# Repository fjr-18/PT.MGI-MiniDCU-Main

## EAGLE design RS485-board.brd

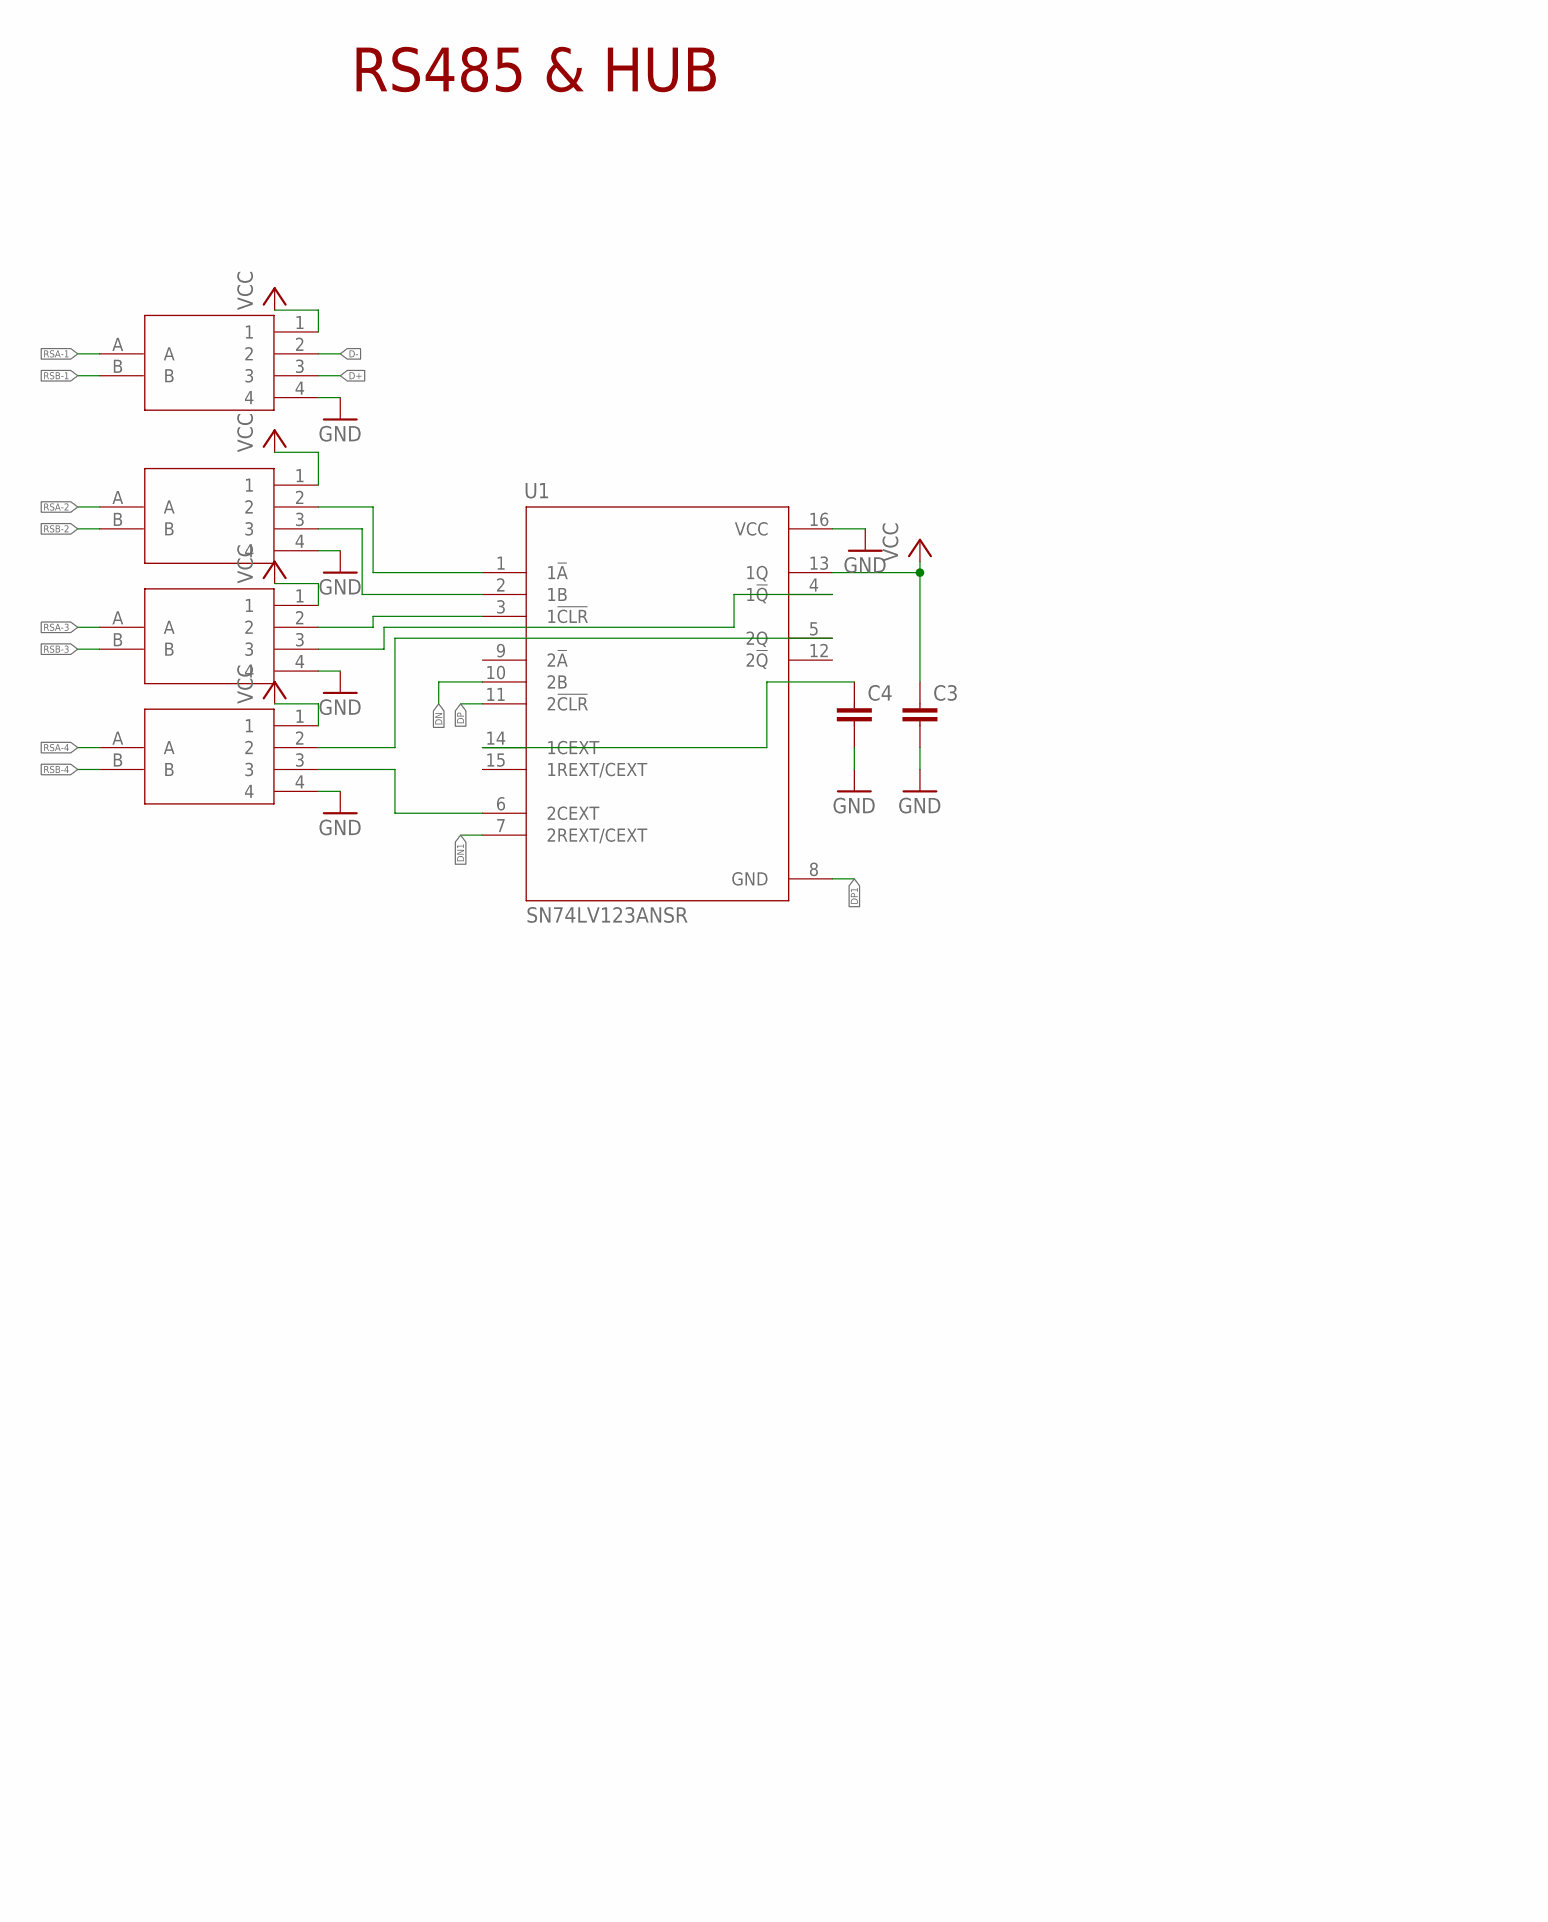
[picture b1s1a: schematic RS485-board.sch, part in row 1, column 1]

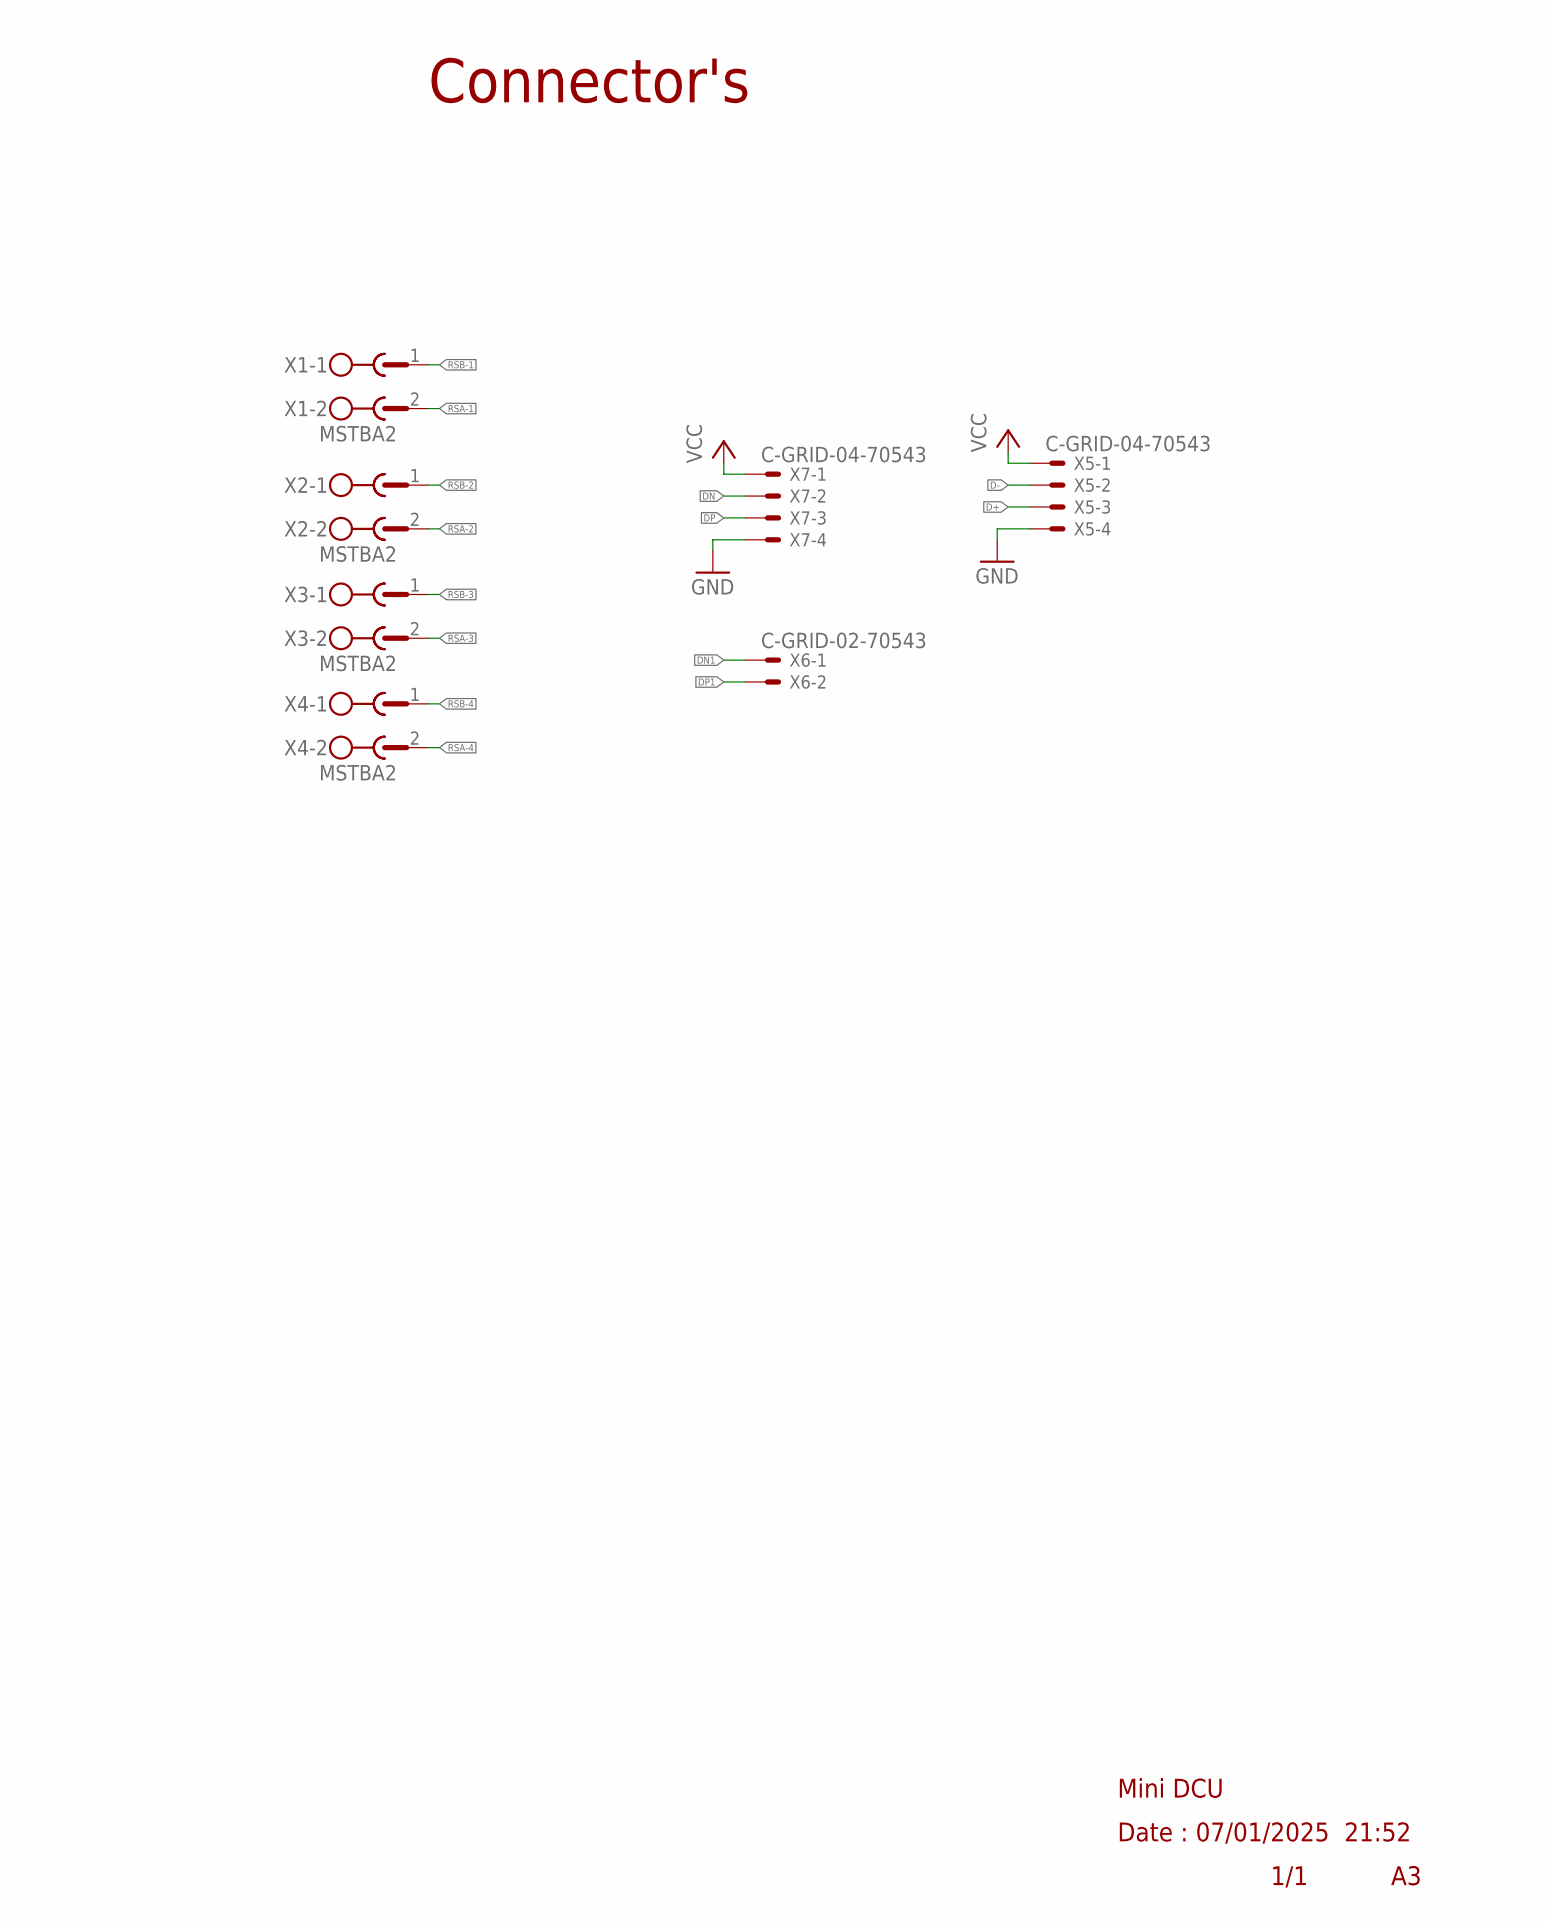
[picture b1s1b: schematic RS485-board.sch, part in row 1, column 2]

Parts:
C3, C4: C-EUC0603K; C0603K
U1: SN74LV123ANSR; SOIC127P780X200-16N
USB2RS1, USB2RS2, USB2RS3, USB2RS5: USB2RS485
X1, X2, X3, X4: MSTBA2
X5, X7: C-GRID-04-70543; 70543-04
X6: C-GRID-02-70543; 70543-02

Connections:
D+: USB2RS5.3, X5.3
D-: USB2RS5.2, X5.2
DN: U1.10 (2B), X7.2
DN1: U1.7 (2REXT/CEXT), X6.1
DP: U1.11 (2!CLR), X7.3
DP1: U1.8 (GND), X6.2
GND: C3.2, C4.2, U1.16 (VCC), USB2RS1.4, USB2RS2.4, USB2RS3.4, USB2RS5.4, X5.4, X7.4
unnamed: U1.1 (1!A), USB2RS1.2
unnamed: U1.2 (1B), USB2RS1.3
unnamed: U1.3 (1!CLR), USB2RS2.2
unnamed: U1.4 (1!Q), USB2RS2.3
unnamed: U1.5 (2Q), USB2RS3.2
unnamed: U1.6 (2CEXT), USB2RS3.3
unnamed: C4.1, U1.14 (1CEXT)
RSA-1: USB2RS5.A, X1.2
RSA-2: USB2RS1.A, X2.2
RSA-3: USB2RS2.A, X3.2
RSA-4: USB2RS3.A, X4.2
RSB-1: USB2RS5.B, X1.1
RSB-2: USB2RS1.B, X2.1
RSB-3: USB2RS2.B, X3.1
RSB-4: USB2RS3.B, X4.1
VCC: C3.1, U1.13 (1Q), USB2RS1.1, USB2RS2.1, USB2RS3.1, USB2RS5.1, X5.1, X7.1

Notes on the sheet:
Mini DCU
Date : 07/01/2025 21:52
1/1
Connector's
RS485 & HUB

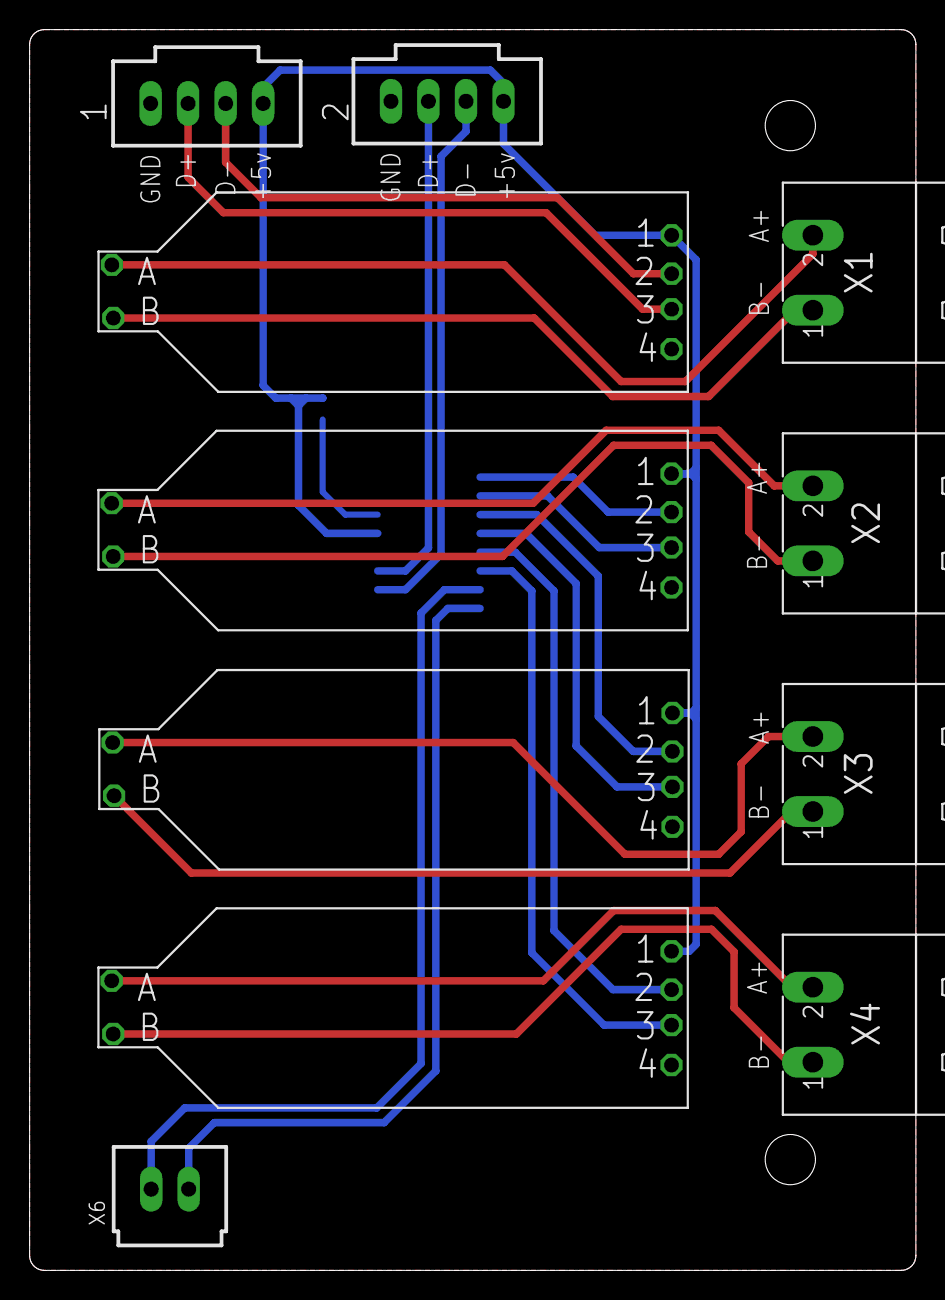
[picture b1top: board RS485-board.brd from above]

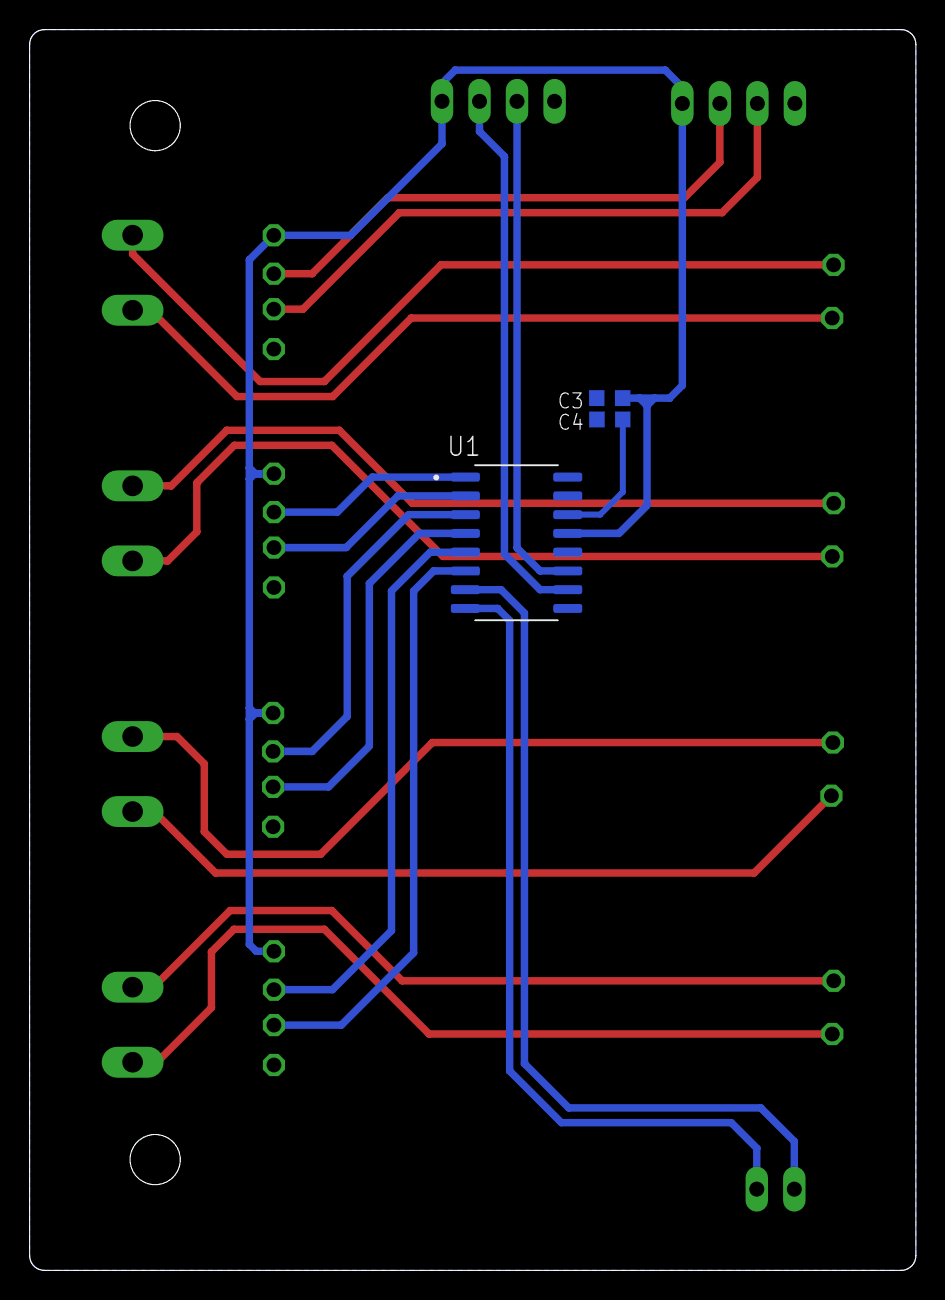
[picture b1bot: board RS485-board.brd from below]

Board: 2 copper layers, 60.0 x 84.0 mm, 14 parts (3 on the bottom side), 23 nets.
